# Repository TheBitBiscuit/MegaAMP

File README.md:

# MegaAMP
 Audio filter and amplifier for Sega Genesis/Mega Drive.  Board and Schematics were put together with CadSoft Eagle. Mk.I was built and fabbed by OSHpark and installed in one of my own Genesis.

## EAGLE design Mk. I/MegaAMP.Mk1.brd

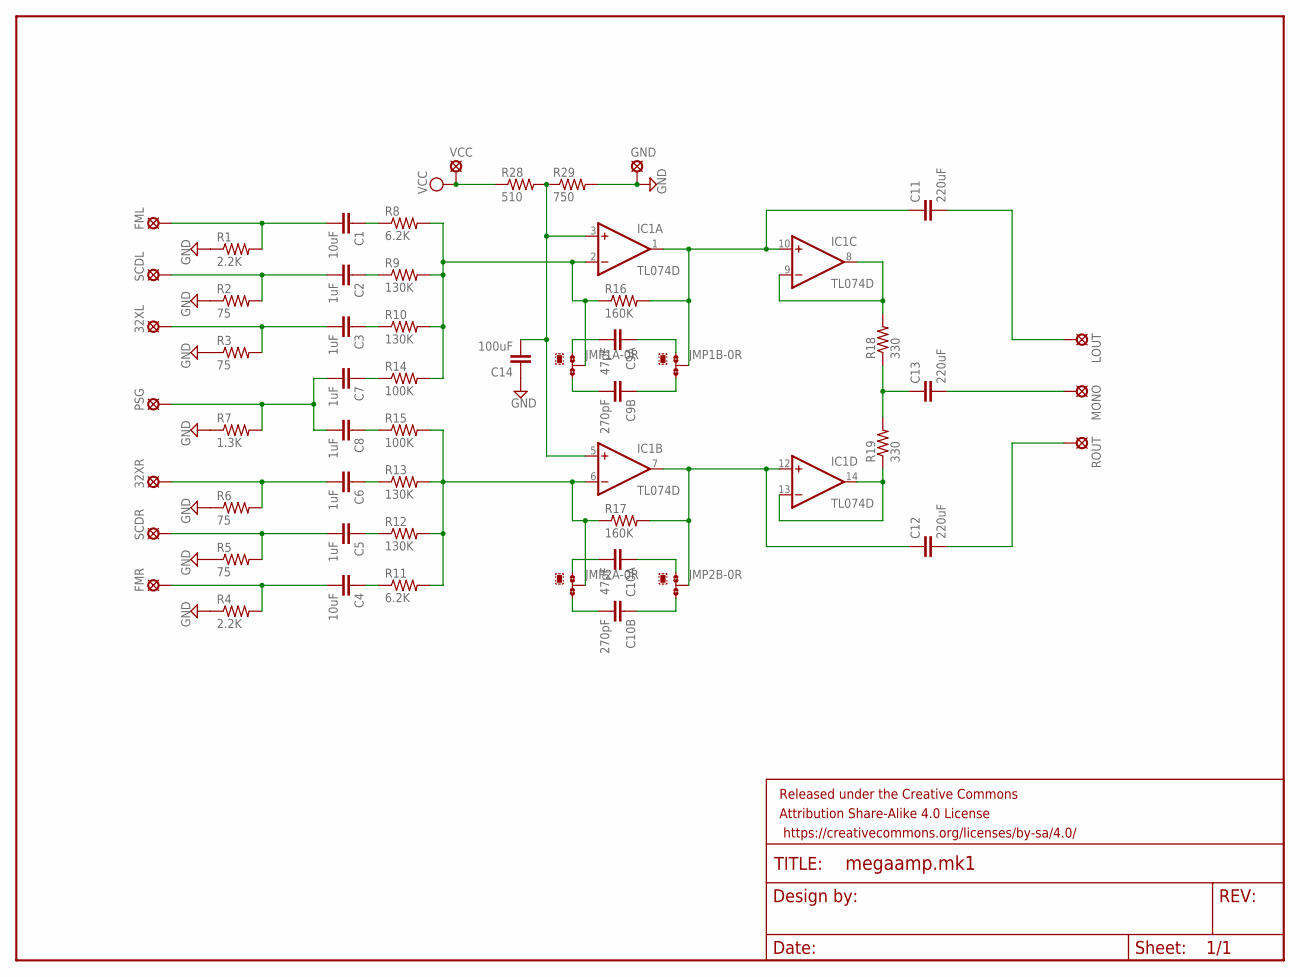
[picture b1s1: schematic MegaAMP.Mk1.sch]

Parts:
32XL, 32XR: LSP13
C1, C4: 10uF; C0805
C2, C3, C5, C6, C7, C8: 1uF; C0805
C9A, C10A: 47pF; C0805
C9B, C10B: 270pF; C0805
C11, C12, C13: 220uF; C1210
C14: 100uF; C1206
FML: LSP13
FMR: LSP13
FRAME1: FRAME-LETTER; CREATIVE_COMMONS
GND: LSP13
IC1: TL074D; SO14
JMP1A, JMP1B, JMP2A, JMP2B: 0R-JUMPA; A0R-JMP
LOUT: LSP13
MONO: LSP13
PSG: LSP13
R1, R4: 2.2K; R0805
R2, R3, R5, R6: 75; R0805
R7: 1.3K; R0805
R8, R11: 6.2K; R0805
R9, R10, R12, R13: 130K; R0805
R14, R15: 100K; R0805
R16, R17: 160K; R0805
R18, R19: 330; R0805
R28: 510; R0805
R29: 750; R0805
ROUT: LSP13
SCDL: LSP13
SCDR: LSP13
VCC: LSP13

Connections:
GND: C14.1, GND.MP, R1.1, R2.1, R3.1, R4.1, R5.1, R6.1, R7.1, R29.2
unnamed: C11.1, IC1.1 (OUT), IC1.10 (+IN), JMP1B.2, R16.2
unnamed: C13.1, R18.1, R19.2
unnamed: R28.1, VCC.MP
unnamed: C12.2, ROUT.MP
unnamed: C14.2, IC1.3 (+IN), IC1.5 (+IN), R28.2, R29.1
unnamed: IC1.8 (OUT), IC1.9 (-IN), R18.2
unnamed: C9A.2, JMP1A.1
unnamed: IC1.13 (-IN), IC1.14 (OUT), R19.1
unnamed: C9A.1, JMP1B.1
unnamed: C9B.2, JMP1A.3
unnamed: C9B.1, JMP1B.3
unnamed: C12.1, IC1.7 (OUT), IC1.12 (+IN), JMP2B.2, R17.2
unnamed: C10A.2, JMP2A.1
unnamed: C10A.1, JMP2B.1
unnamed: C10B.2, JMP2A.3
unnamed: C10B.1, JMP2B.3
unnamed: C11.2, LOUT.MP
unnamed: C13.2, MONO.MP
unnamed: C1.2, FML.MP, R1.2
unnamed: C2.2, R2.2, SCDL.MP
unnamed: 32XL.MP, C3.2, R3.2
unnamed: C7.2, C8.2, PSG.MP, R7.2
unnamed: 32XR.MP, C6.2, R6.2
unnamed: C5.2, R5.2, SCDR.MP
unnamed: C4.2, FMR.MP, R4.2
unnamed: C1.1, R8.1
unnamed: C2.1, R9.1
unnamed: C3.1, R10.1
unnamed: C7.1, R14.1
unnamed: C8.1, R15.1
unnamed: C6.1, R13.1
unnamed: C5.1, R12.1
unnamed: C4.1, R11.1
unnamed: IC1.2 (-IN), JMP1A.2, R8.2, R9.2, R10.2, R14.2, R16.1
unnamed: IC1.6 (-IN), JMP2A.2, R11.2, R12.2, R13.2, R15.2, R17.1
V+: IC1.4 (V+)
V-: IC1.11 (V-)

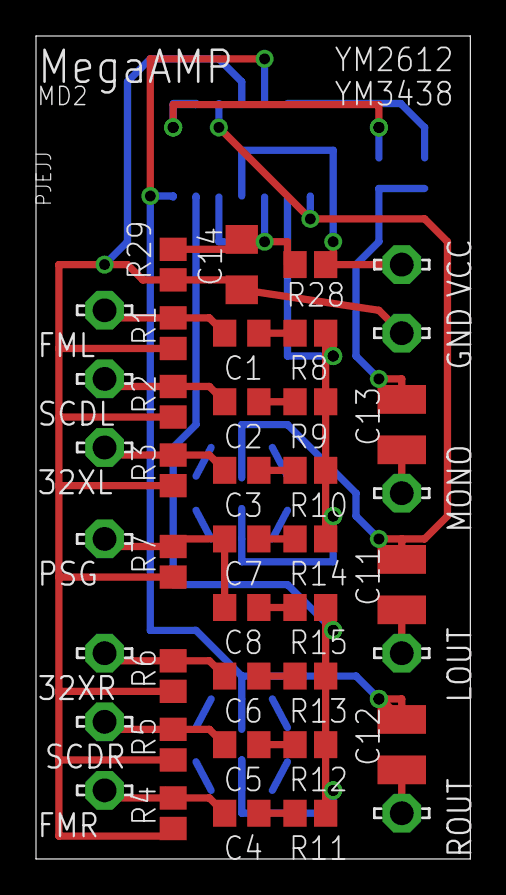
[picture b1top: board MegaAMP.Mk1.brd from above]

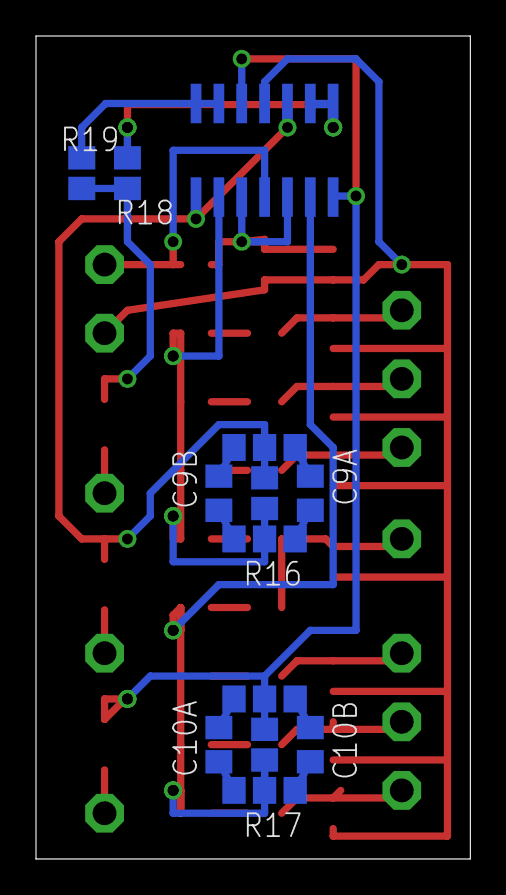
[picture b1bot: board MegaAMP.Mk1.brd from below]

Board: 2 copper layers, 24.1 x 45.7 mm, 55 parts (13 on the bottom side), 36 nets.

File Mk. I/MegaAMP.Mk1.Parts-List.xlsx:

MegaAMP Mk. I Parts List
Name | Value | Package | Digikey Part # | Notes
R1 - Note 1 | 2.2K | 0805 | 311-2.20KCRCT-ND | Note 1
R2 - Note 2 | 75 | 0805 | 311-75.0CRCT-ND | 2.2Kohm pull-down resistors
R3 - Note 2 | 75 | 0805 | 311-75.0CRCT-ND | are only required if fitting a
R4 - Note 1 | 2.2K | 0805 | 311-2.20KCRCT-ND | YM2612 into system with
R5 - Note 2 | 75 | 0805 | 311-75.0CRCT-ND | ASIC YM3438. Already on
R6 - Note 2 | 75 | 0805 | 311-75.0CRCT-ND | the board of YM2612.
R7 | 1.3K | 0805 | 311-1.30KCRCT-ND
R8 - Note 3 | 6.2K - YM2612 | 0805 | 311-6.20KCRCT-ND | Note 2
 | 51K - YM3438 | 0805 | 311-51.0KCRCT-ND | 75ohm pull-down resistors
R9 | 130K | 0805 | 311-130KCRCT-ND | on CD & 32X audio inputs are
R10 | 130K | 0805 | 311-130KCRCT-ND | already present on the board
R11 - Note 3 | 6.2K - YM2612 | 0805 | 311-6.20KCRCT-ND | and can be omitted.
 | 51K - YM3438 | 0805 | 311-51.0KCRCT-ND | (Required on 32X inputs if
R12 | 130K | 0805 | 311-130KCRCT-ND | fitting YM2612 in a VA0 to
R13 | 130K | 0805 | 311-130KCRCT-ND | VA1.8 Model 2)
R14 | 100K | 0805 | 311-100KCRCT-ND
R15 | 100K | 0805 | 311-100KCRCT-ND | Note 3
R16 | 160K | 0805 | 311-160KCRCT-ND | This resistor's value changes
R17 | 160K | 0805 | 311-160KCRCT-ND | depending on what audio
R18 | 330 | 0805 | 311-330CRCT-ND | processor is being used.
R19 | 330 | 0805 | 311-330CRCT-ND | On a YM2612 system, use
R28 | 510 | 0805 | 311-510CRCT-ND | 6.2Kohm.
R29 | 750 | 0805 | 311-750CRCT-ND | On a YM3438 system, use
C1 | 10uF | 0805 | 1276-2891-1-ND | 51Kohm.
C2 | 1uF | 0805 | 1276-1066-1-ND
C3 | 1uF | 0805 | 1276-1066-1-ND
C4 | 10uF | 0805 | 1276-2891-1-ND
C5 | 1uF | 0805 | 1276-1066-1-ND
C6 | 1uF | 0805 | 1276-1066-1-ND
C7 | 1uF | 0805 | 1276-1066-1-ND
C8 | 1uF | 0805 | 1276-1066-1-ND
C9A | 0.47pF | 0805 | 1276-2700-1-ND
C9B | 270pF | 0805 | 1276-1262-1-ND
C10A | 0.47pF | 0805 | 1276-2700-1-ND
C10B | 270pF | 0805 | 1276-1262-1-ND
C11 | 220uF | 1210 | 1276-3375-1-ND
C12 | 220uF | 1210 | 1276-3375-1-ND
C13 | 220uF | 1210 | 1276-3375-1-ND
C14 | 100uF | 1206 | 1276-1782-1-ND
TL074CDR | OPAMP | 14SOIC | 296-1283-1-ND
 |  |  |  | PJEJJ 2014

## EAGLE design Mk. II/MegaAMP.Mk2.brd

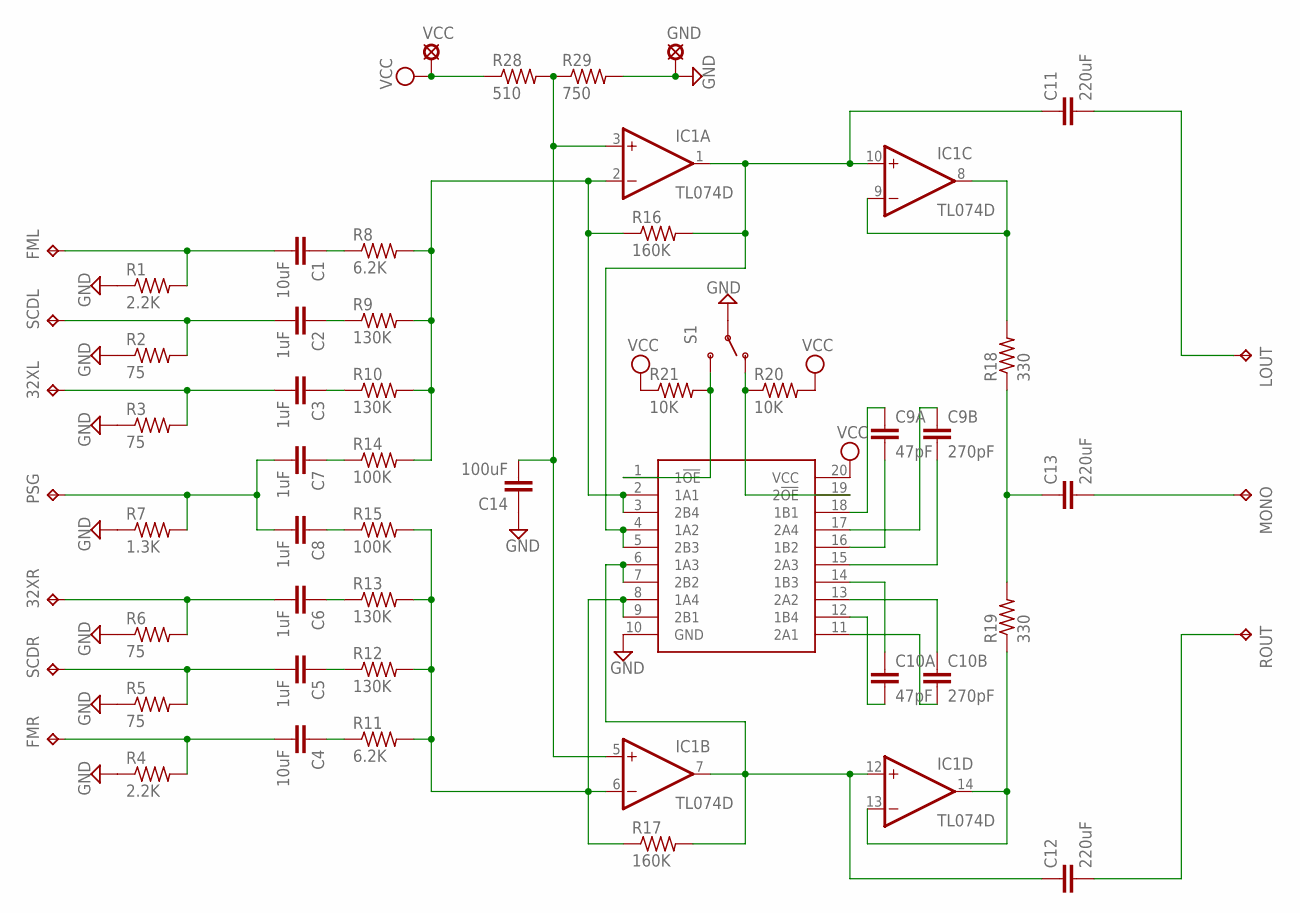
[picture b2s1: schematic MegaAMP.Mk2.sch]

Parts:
32XL, 32XR: TPTP20R; TP20R
C1, C4: 10uF; C0805
C2, C3, C5, C6, C7, C8: 1uF; C0805
C9A, C10A: 47pF; C0805
C9B, C10B: 270pF; C0805
C11, C12, C13: 220uF; C1210
C14: 100uF; C1206
FML: TPTP20R; TP20R
FMR: TPTP20R; TP20R
GND: LSP13
IC1: TL074D; SO14
LOUT: TPTP20R; TP20R
MONO: TPTP20R; TP20R
PSG: TPTP20R; TP20R
R1, R4: 2.2K; R0805
R2, R3, R5, R6: 75; R0805
R7: 1.3K; R0805
R8, R11: 6.2K; R0805
R9, R10, R12, R13: 130K; R0805
R14, R15: 100K; R0805
R16, R17: 160K; R0805
R18, R19: 330; R0805
R20, R21: 10K; R0805
R28: 510; R0805
R29: 750; R0805
ROUT: TPTP20R; TP20R
S1: SWITCH-SPDTPTH; SWITCH-SPDT
SCDL: TPTP20R; TP20R
SCDR: TPTP20R; TP20R
U$1: DBQ(R-PDS0-G20); DBQ(R-PDSO-G20)
VCC: LSP13

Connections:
GND: C14.1, GND.MP, R1.1, R2.1, R3.1, R4.1, R5.1, R6.1, R7.1, R29.2, S1.2, U$1.10 (GND)
unnamed: IC1.2 (-IN), R8.2, R9.2, R10.2, R14.2, R16.1, U$1.2 (1A1), U$1.3 (2B4)
unnamed: C13.1, R18.1, R19.2
unnamed: R21.2, S1.3 (S), U$1.1 (1!OE)
unnamed: C12.2, ROUT.TP
unnamed: C14.2, IC1.3 (+IN), IC1.5 (+IN), R28.2, R29.1
unnamed: C9A.1, U$1.18 (1B1)
unnamed: IC1.8 (OUT), IC1.9 (-IN), R18.2
unnamed: C9A.2, U$1.16 (1B2)
unnamed: IC1.13 (-IN), IC1.14 (OUT), R19.1
unnamed: C10A.1, U$1.14 (1B3)
unnamed: C10A.2, U$1.12 (1B4)
unnamed: R20.1, S1.1 (O), U$1.19 (2!OE)
unnamed: C12.1, IC1.7 (OUT), IC1.12 (+IN), R17.2, U$1.6 (1A3), U$1.7 (2B2)
unnamed: C9B.1, U$1.17 (2A4)
unnamed: C9B.2, U$1.15 (2A3)
unnamed: C10B.1, U$1.13 (2A2)
unnamed: C10B.2, U$1.11 (2A1)
unnamed: IC1.6 (-IN), R11.2, R12.2, R13.2, R15.2, R17.1, U$1.8 (1A4), U$1.9 (2B1)
unnamed: C11.2, LOUT.TP
unnamed: C13.2, MONO.TP
unnamed: C1.2, FML.TP, R1.2
unnamed: C2.2, R2.2, SCDL.TP
unnamed: 32XL.TP, C3.2, R3.2
unnamed: C7.2, C8.2, PSG.TP, R7.2
unnamed: 32XR.TP, C6.2, R6.2
unnamed: C5.2, R5.2, SCDR.TP
unnamed: C4.2, FMR.TP, R4.2
unnamed: C1.1, R8.1
unnamed: C2.1, R9.1
unnamed: C3.1, R10.1
unnamed: C7.1, R14.1
unnamed: C8.1, R15.1
unnamed: C6.1, R13.1
unnamed: C5.1, R12.1
unnamed: C4.1, R11.1
unnamed: C11.1, IC1.1 (OUT), IC1.10 (+IN), R16.2, U$1.4 (1A2), U$1.5 (2B3)
V+: IC1.4 (V+)
V-: IC1.11 (V-)
VCC: R20.2, R21.1, R28.1, U$1.20 (VCC), VCC.MP

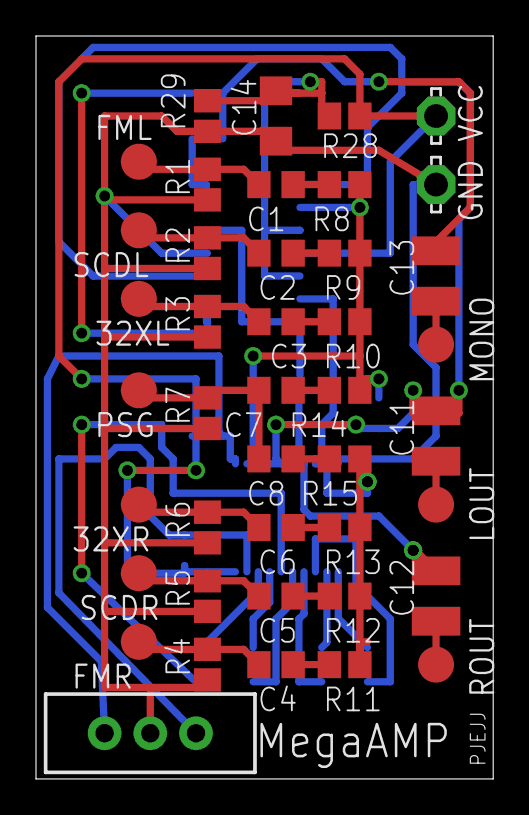
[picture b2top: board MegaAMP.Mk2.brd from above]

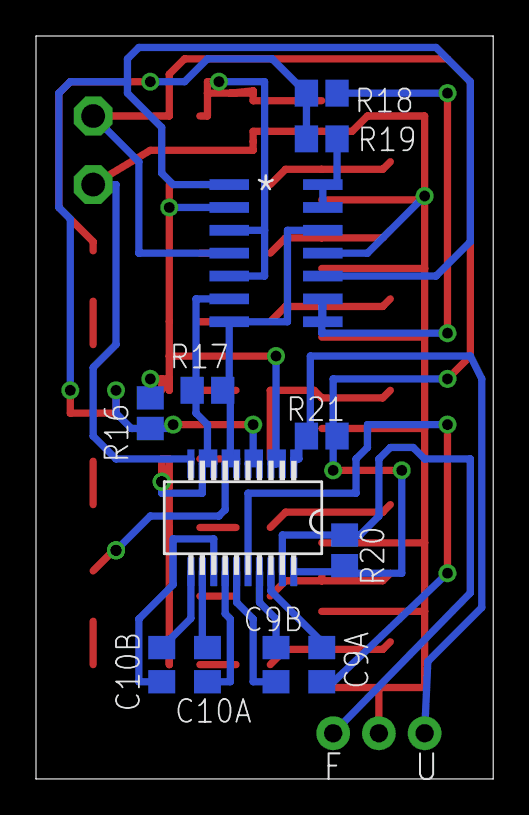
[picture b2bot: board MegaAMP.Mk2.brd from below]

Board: 2 copper layers, 25.4 x 41.3 mm, 54 parts (12 on the bottom side), 38 nets.

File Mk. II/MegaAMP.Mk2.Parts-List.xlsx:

MegaAMP Mk. II Parts List
Name | Value | Package | Digikey Part # | Notes
R1 - Note 1 | 2.2K | 0805 | 311-2.20KCRCT-ND | Note 1
R2 - Note 2 | 75 | 0805 | 311-75.0CRCT-ND | 2.2Kohm pull-down resistors
R3 - Note 2 | 75 | 0805 | 311-75.0CRCT-ND | are only required if fitting a
R4 - Note 1 | 2.2K | 0805 | 311-2.20KCRCT-ND | YM2612 into system with
R5 - Note 2 | 75 | 0805 | 311-75.0CRCT-ND | ASIC YM3438. Already on
R6 - Note 2 | 75 | 0805 | 311-75.0CRCT-ND | the board of YM2612.
R7 | 1.3K | 0805 | 311-1.30KCRCT-ND
R8 - Note 3 | 6.2K - YM2612 | 0805 | 311-6.20KCRCT-ND | Note 2
 | 51K - YM3438 | 0805 | 311-51.0KCRCT-ND | 75ohm pull-down resistors
R9 | 130K | 0805 | 311-130KCRCT-ND | on CD & 32X audio inputs are
R10 | 130K | 0805 | 311-130KCRCT-ND | already present on the board
R11 - Note 3 | 6.2K - YM2612 | 0805 | 311-6.20KCRCT-ND | and can be omitted.
 | 51K - YM3438 | 0805 | 311-51.0KCRCT-ND | (Required on 32X inputs if
R12 | 130K | 0805 | 311-130KCRCT-ND | fitting YM2612 in a VA0 to
R13 | 130K | 0805 | 311-130KCRCT-ND | VA1.8 Model 2)
R14 | 100K | 0805 | 311-100KCRCT-ND
R15 | 100K | 0805 | 311-100KCRCT-ND | Note 3
R16 | 160K | 0805 | 311-160KCRCT-ND | This resistor's value changes
R17 | 160K | 0805 | 311-160KCRCT-ND | depending on what audio
R18 | 330 | 0805 | 311-330CRCT-ND | processor is being used.
R19 | 330 | 0805 | 311-330CRCT-ND | On a YM2612 system, use
R20 | 10K | 0805 | 311-10.0KCRCT-ND | 6.2Kohm.
R21 | 10K | 0805 | 311-10.0KCRCT-ND | On a YM3438 system, use
R28 | 510 | 0805 | 311-510CRCT-ND | 51Kohm.
R29 | 750 | 0805 | 311-750CRCT-ND
C1 | 10uF | 0805 | 1276-2891-1-ND
C2 | 1uF | 0805 | 1276-1066-1-ND
C3 | 1uF | 0805 | 1276-1066-1-ND
C4 | 10uF | 0805 | 1276-2891-1-ND
C5 | 1uF | 0805 | 1276-1066-1-ND
C6 | 1uF | 0805 | 1276-1066-1-ND
C7 | 1uF | 0805 | 1276-1066-1-ND
C8 | 1uF | 0805 | 1276-1066-1-ND
C9A | 0.47pF | 0805 | 1276-2700-1-ND
C9B | 270pF | 0805 | 1276-1262-1-ND
C10A | 0.47pF | 0805 | 1276-2700-1-ND
C10B | 270pF | 0805 | 1276-1262-1-ND
C11 | 220uF | 1210 | 1276-3375-1-ND
C12 | 220uF | 1210 | 1276-3375-1-ND
C13 | 220uF | 1210 | 1276-3375-1-ND
C14 | 100uF | 1206 | 1276-1782-1-ND
SN74CBT3244 | BUS SWITCH | 20QSOP | 296-19193-1-ND
TL074CDR | OPAMP | 14SOIC | 296-1283-1-ND
SPDT or Jumper
 |  |  |  | PJEJJ 2014

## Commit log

2023-05-29 Migrate to GitHub

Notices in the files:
parts and their libraries:
SparkFun-Aesthetics: Licensing: Creative Commons ShareAlike 4.0 International - https://creativecommons.org/licenses/by-sa/4.0
SparkFun-Aesthetics: Released under the Creative Commons Attribution Share-Alike 4.0 License
SparkFun-Aesthetics: https://creativecommons.org/licenses/by-sa/4.0
